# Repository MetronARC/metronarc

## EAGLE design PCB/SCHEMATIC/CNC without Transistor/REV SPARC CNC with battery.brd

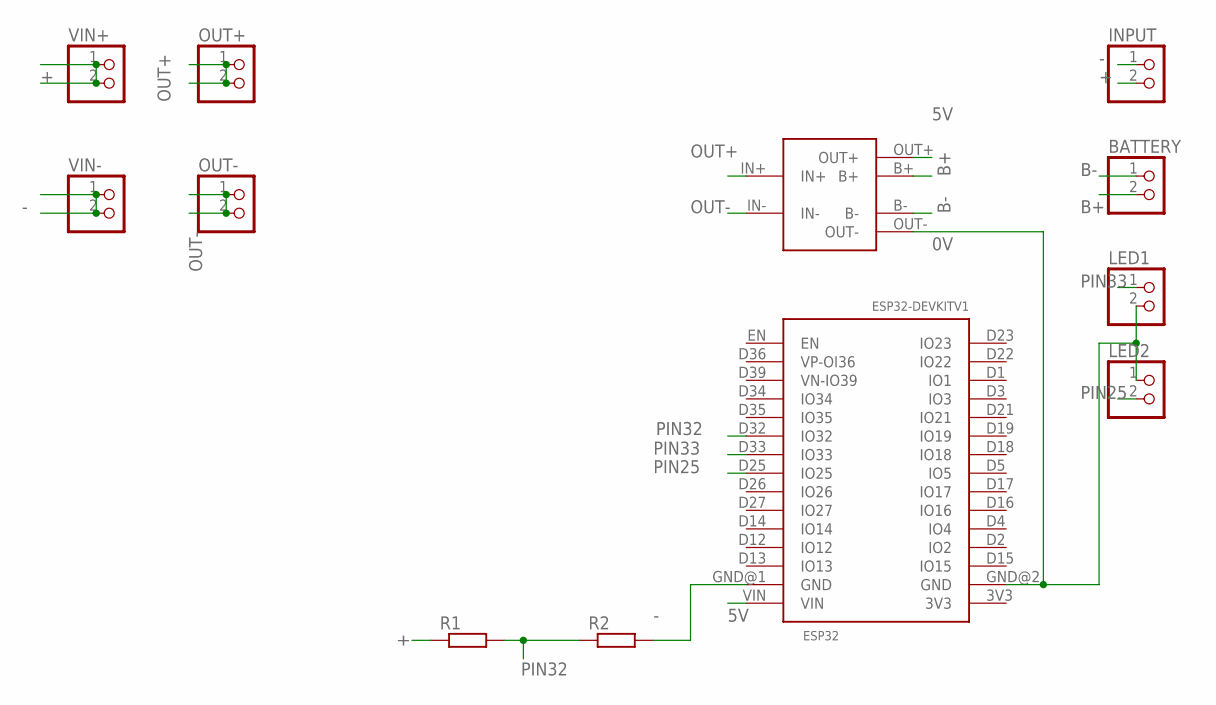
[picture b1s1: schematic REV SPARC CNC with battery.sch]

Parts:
BATTERY: PINHD-1X02_2.54; 1X02
ESP32: ESP32DEVKITV1; ESP32-DEVKITV1
INPUT: PINHD-1X2; 1X02
LED1, LED2: PINHD-1X2; 1X02
OUT+: PINHD-1X2; 1X02
OUT-: PINHD-1X2; 1X02
R1, R2: R-EU_0207/10; 0207/10
TP: TP4056-PTH
VIN+: PINHD-1X2; 1X02
VIN-: PINHD-1X2; 1X02

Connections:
0V: ESP32.GND@2 (GND), LED1.2, LED2.1, TP.OUT-
5V: ESP32.VIN, TP.OUT+
+: INPUT.2, R1.1, VIN+.1, VIN+.2
-: ESP32.GND@1 (GND), INPUT.1, R2.2, VIN-.1, VIN-.2
B+: BATTERY.2, TP.B+
B-: BATTERY.1, TP.B-
OUT+: OUT+.1, OUT+.2, TP.IN+
OUT-: OUT-.1, OUT-.2, TP.IN-
PIN25: ESP32.D25 (IO25), LED2.2
PIN32: ESP32.D32 (IO32), R1.2, R2.1
PIN33: ESP32.D33 (IO33), LED1.1

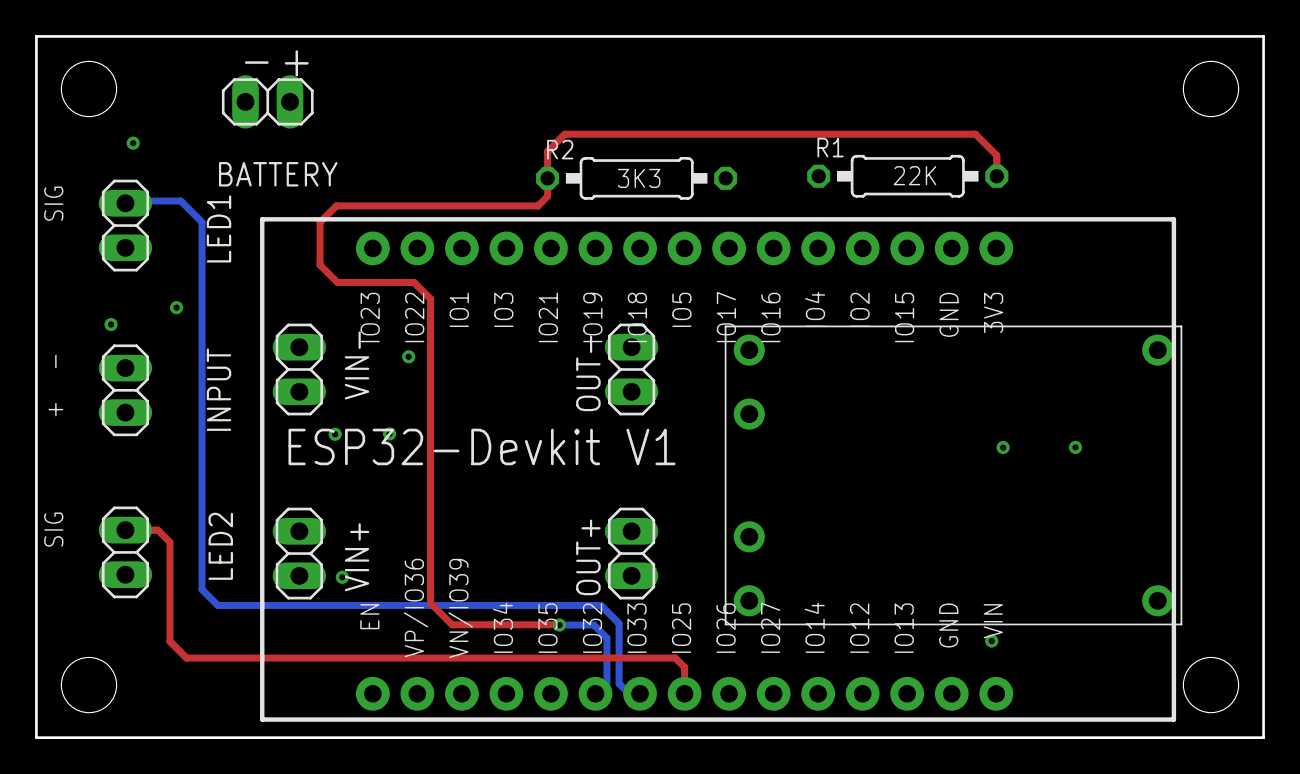
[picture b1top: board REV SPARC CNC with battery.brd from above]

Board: 4 copper layers, 70.0 x 40.0 mm, 12 parts (0 on the bottom side), 11 nets.

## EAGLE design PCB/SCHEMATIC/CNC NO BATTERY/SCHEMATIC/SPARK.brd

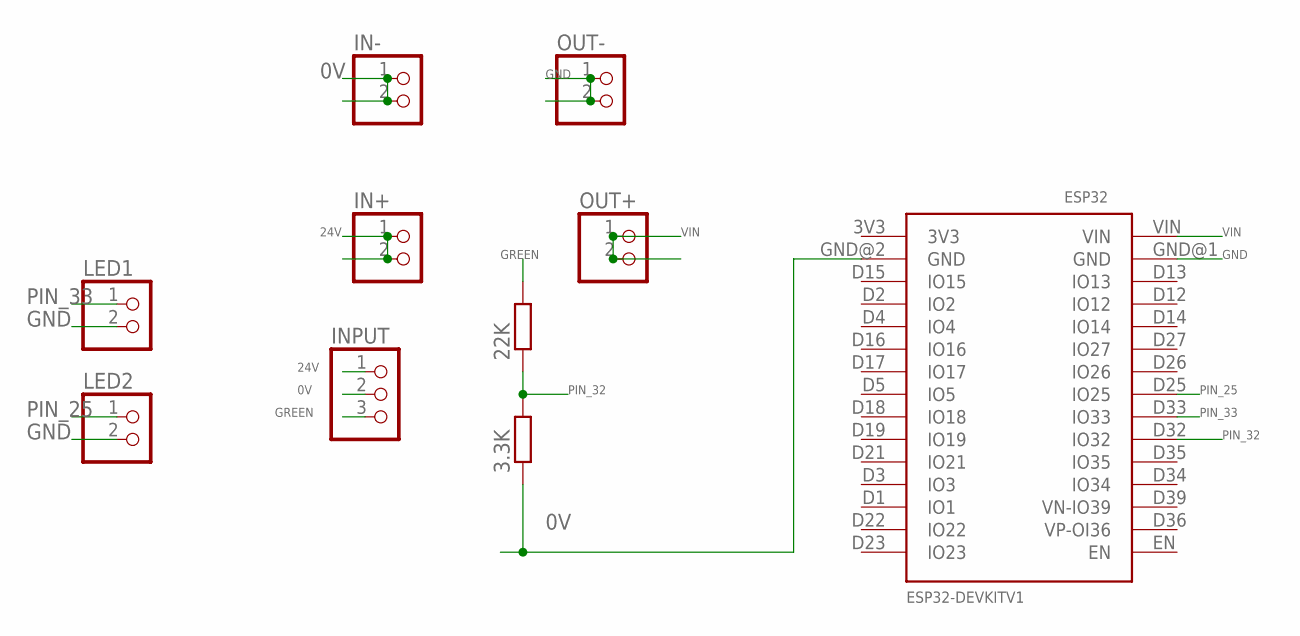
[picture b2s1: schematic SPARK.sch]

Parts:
3.3K, 22K: R-EU_0207/10; 0207/10
ESP32: ESP32DEVKITV1; ESP32-DEVKITV1
IN+: PINHD-1X2; 1X02
IN-: PINHD-1X2; 1X02
INPUT: PINHD-1X3; 1X03
LED1, LED2: PINHD-1X2; 1X02
OUT+: PINHD-1X2; 1X02
OUT-: PINHD-1X2; 1X02

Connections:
0V: 3.3K.1, ESP32.GND@2 (GND), IN-.1, IN-.2, INPUT.2
24V: IN+.1, IN+.2, INPUT.1
GND: ESP32.GND@1 (GND), LED1.2, LED2.2, OUT-.1, OUT-.2
GREEN: 22K.2, INPUT.3
PIN_25: ESP32.D25 (IO25), LED2.1
PIN_32: 3.3K.2, 22K.1, ESP32.D32 (IO32)
PIN_33: ESP32.D33 (IO33), LED1.1
VIN: ESP32.VIN, OUT+.1, OUT+.2

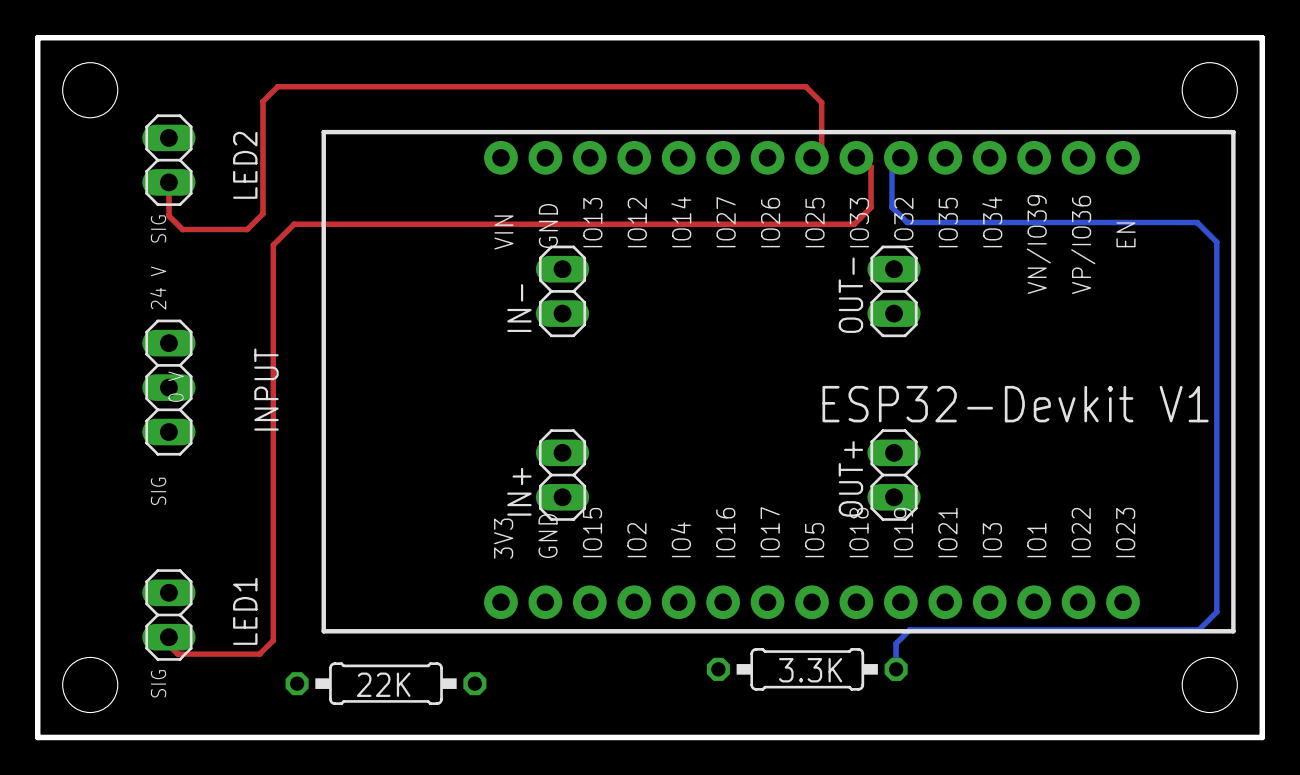
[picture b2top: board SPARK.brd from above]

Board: 4 copper layers, 70.0 x 40.0 mm, 10 parts (0 on the bottom side), 8 nets.

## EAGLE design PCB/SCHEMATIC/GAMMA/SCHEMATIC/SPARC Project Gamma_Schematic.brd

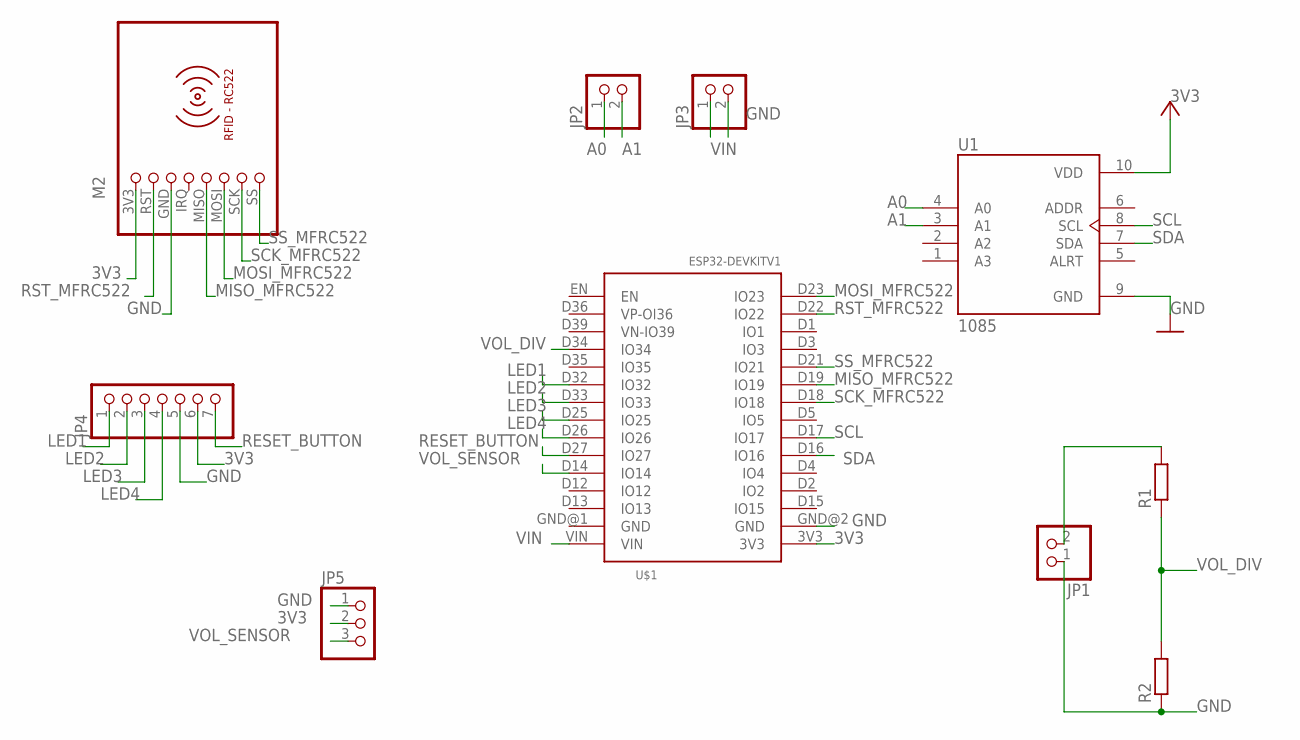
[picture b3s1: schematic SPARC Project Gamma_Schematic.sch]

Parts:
JP1, JP2, JP3: PINHD-1X2; 1X02
JP4: PINHD-1X7; 1X07
JP5: PINHD-1X3; 1X03
M2: RFID-RC522
R1, R2: R-EU_0204/2V; 0204V
U1: 1085; MODULE_1085
U$1: ESP32DEVKITV1; ESP32-DEVKITV1

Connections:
3V3: JP4.6, JP5.2, M2.3V3 (1), U1.10 (VDD), U$1.3V3
A0: JP2.1, U1.4 (A0)
A1: JP2.2, U1.3 (A1)
GND: JP1.1, JP3.2, JP4.5, JP5.1, M2.GND (3), R2.1, U1.9 (GND), U$1.GND@2 (GND)
LED1: JP4.1, U$1.D32 (IO32)
LED2: JP4.2, U$1.D33 (IO33)
LED3: JP4.3, U$1.D25 (IO25)
LED4: JP4.4, U$1.D26 (IO26)
MISO_MFRC522: M2.MISO (5), U$1.D19 (IO19)
MOSI_MFRC522: M2.MOSI (6), U$1.D23 (IO23)
unnamed: JP1.2, R1.2
RESET_BUTTON: JP4.7, U$1.D27 (IO27)
RST_MFRC522: M2.RST (2), U$1.D22 (IO22)
SCK_MFRC522: M2.SCK (7), U$1.D18 (IO18)
SCL: U1.8 (SCL), U$1.D17 (IO17)
SDA: U1.7 (SDA), U$1.D16 (IO16)
SS_MFRC522: M2.SS (8), U$1.D21 (IO21)
VIN: JP3.1, U$1.VIN
VOL_DIV: R1.1, R2.2, U$1.D34 (IO34)
VOL_SENSOR: JP5.3, U$1.D14 (IO14)

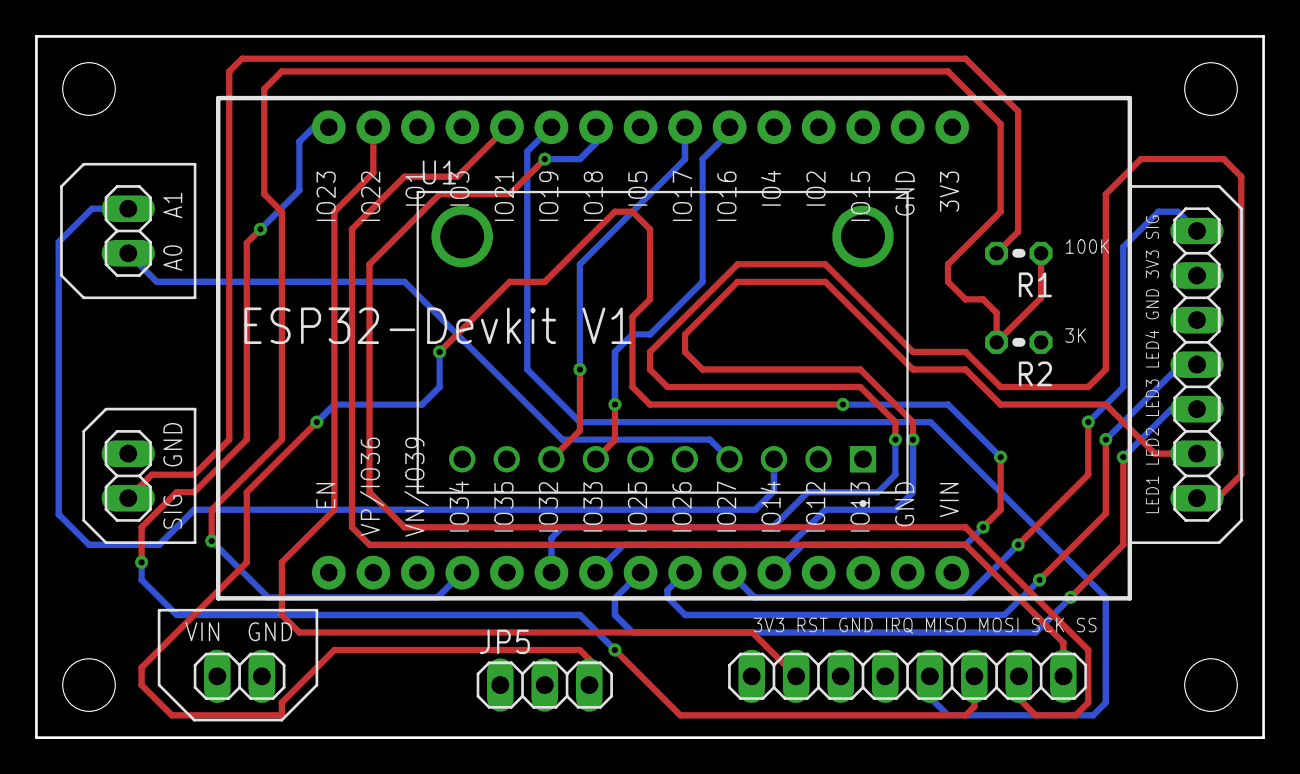
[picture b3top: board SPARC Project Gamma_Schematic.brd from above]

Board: 4 copper layers, 70.0 x 40.0 mm, 10 parts (0 on the bottom side), 20 nets.

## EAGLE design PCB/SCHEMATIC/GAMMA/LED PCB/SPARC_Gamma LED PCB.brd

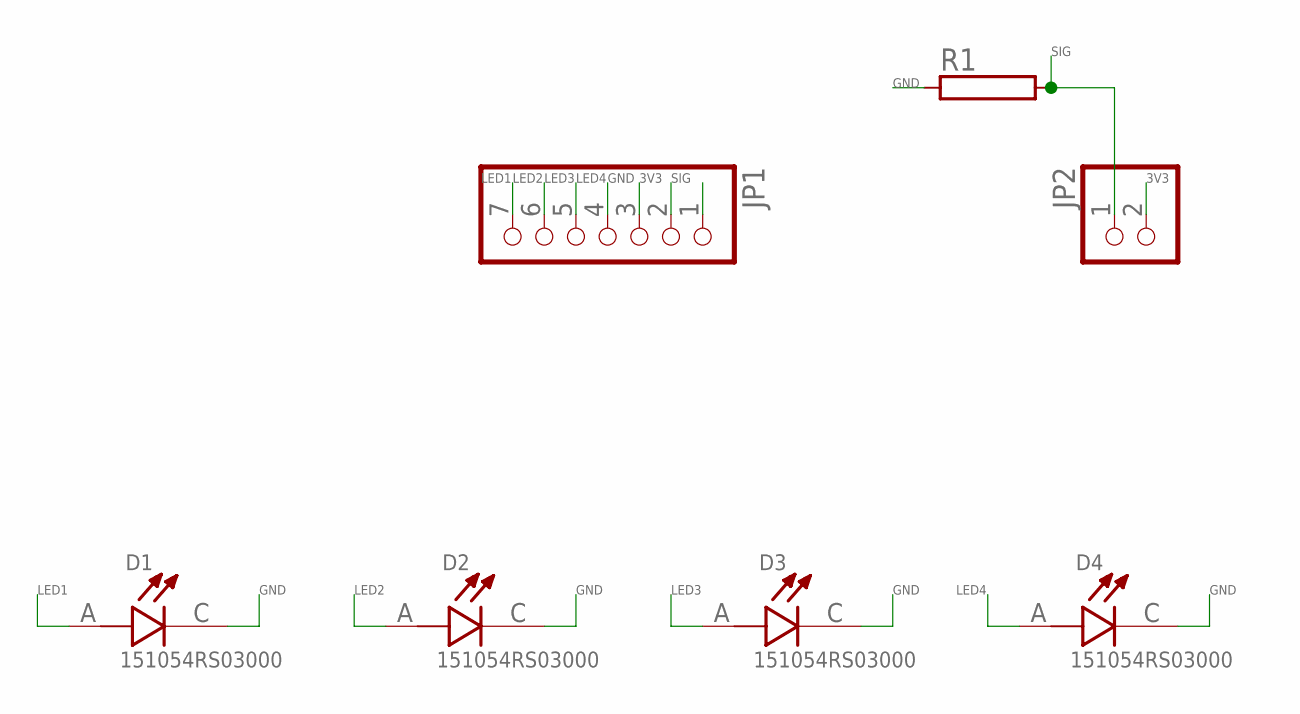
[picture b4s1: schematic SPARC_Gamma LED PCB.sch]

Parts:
D1, D2, D3, D4: 151054RS03000; LED_151054RS03000
JP1: PINHD-1X7; 1X07
JP2: PINHD-1X2; 1X02
R1: RAC01; AC01

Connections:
3V3: JP1.2, JP2.2
GND: D1.C, D2.C, D3.C, D4.C, JP1.3, R1.1
LED1: D1.A, JP1.7
LED2: D2.A, JP1.6
LED3: D3.A, JP1.5
LED4: D4.A, JP1.4
SIG: JP1.1, JP2.1, R1.2

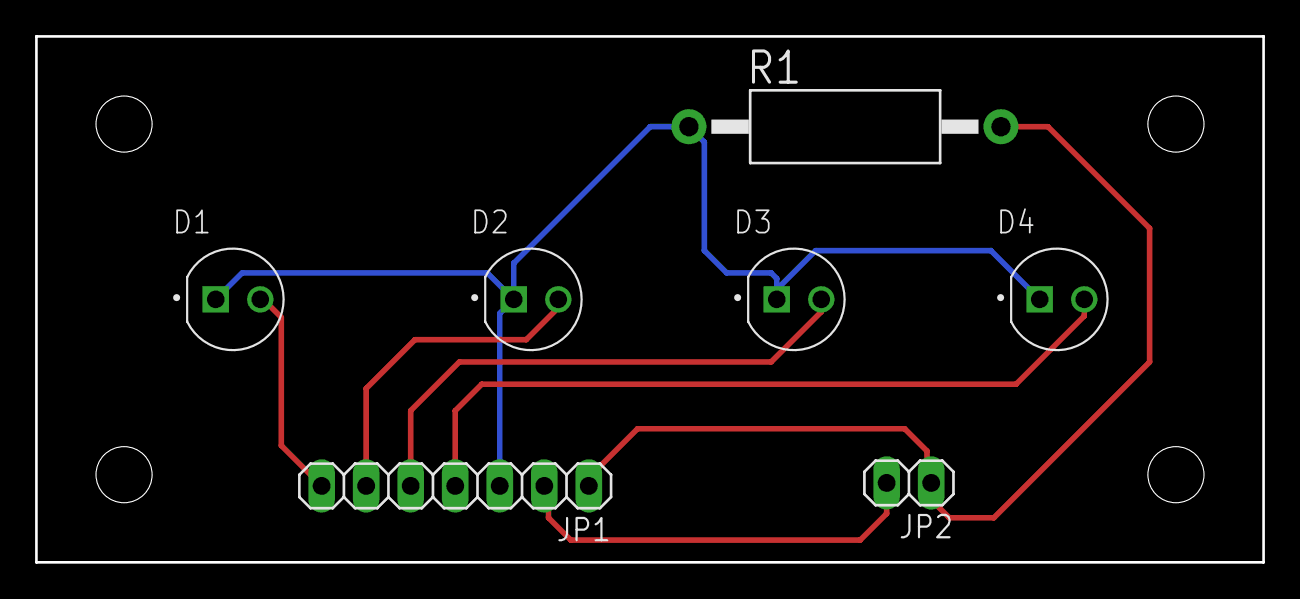
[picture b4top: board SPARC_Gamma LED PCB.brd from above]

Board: 2 copper layers, 70.0 x 30.0 mm, 7 parts (0 on the bottom side), 7 nets.

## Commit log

2024-08-28 added index.html
2024-08-28 Tambah datasheet
2024-08-28 prepare folder
2024-08-28 add file
2024-08-29 Design PCB CNC with battery
2024-08-29 First Source Code Push
2024-08-30 3D PCB CNC with battery
2024-08-30 Added Schematic PCB CNC with Battery
2024-09-06 upload design pcb
2024-09-06 Upload Design CNC STL
2024-09-09 added SPARC Gamma FIle
2024-09-11 Update Revisi Design
2024-09-17 Drawing
2024-09-28 Upload drawing CNC
2024-09-30 Upload Drawing
2024-09-30 Upload drawing Gamma
2024-10-15 Upload STL design GAMMA
2024-10-23 PCB CNC Battery without Transistor
2024-11-25 Schematic wiring CNC and Gamma
2024-12-06 Upload Design Sparc-T Connection Left and Right
2024-12-06 Update Drawing Schematic Sparc CNC
2024-12-10 Upload revisi1 Design Sparc-T connection
2024-12-26 Upload Design Bracket for sparc CNC
2024-12-26 Reupload Design bracket rev 1
2024-12-30 Upload 3 file Drawing Instalation for Sparc CNC
2025-01-10 upload revision for drawing instalation and wiring diagram
2025-02-06 Upload Design Mechanical for OILID Project
2025-02-07 Upload file Etiket and make folder Data
2025-02-07 Upload PCB OILID MINI GAMMA
2025-02-19 Upload design Mini Gamma QR
2025-03-06 Upload SOP FIle for SParc CNC
2025-03-07 Upload SOP for Sparc Gamma
2025-04-08 Upload
